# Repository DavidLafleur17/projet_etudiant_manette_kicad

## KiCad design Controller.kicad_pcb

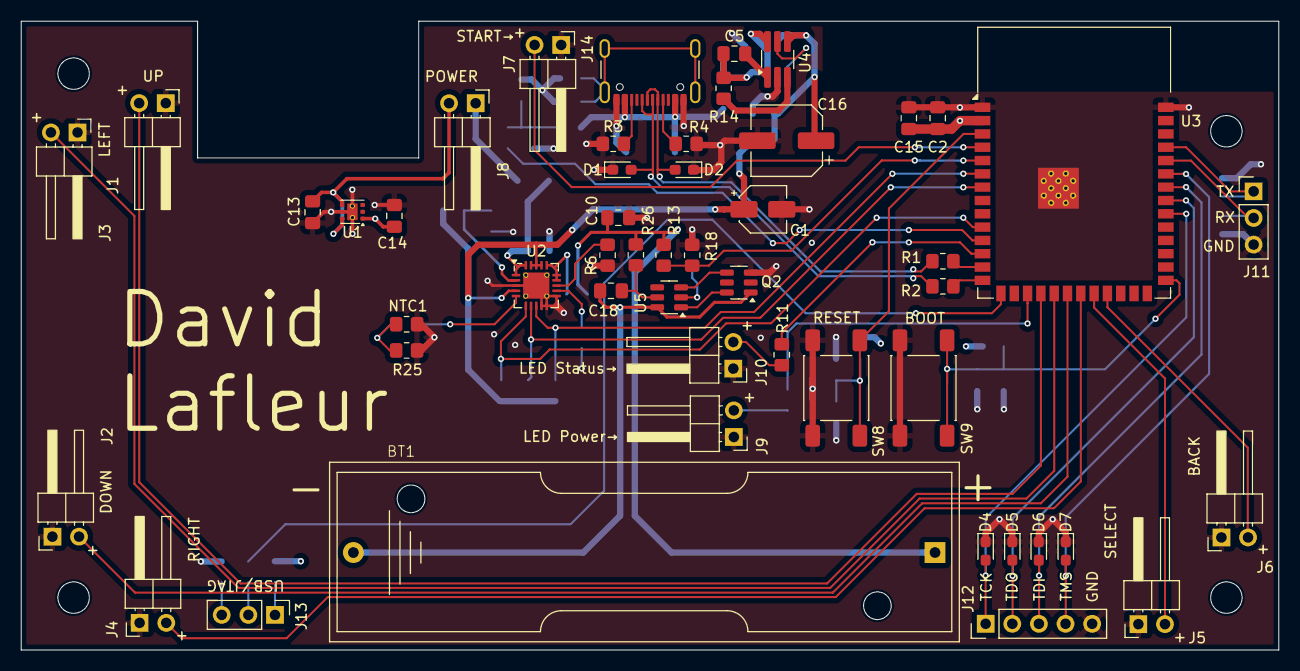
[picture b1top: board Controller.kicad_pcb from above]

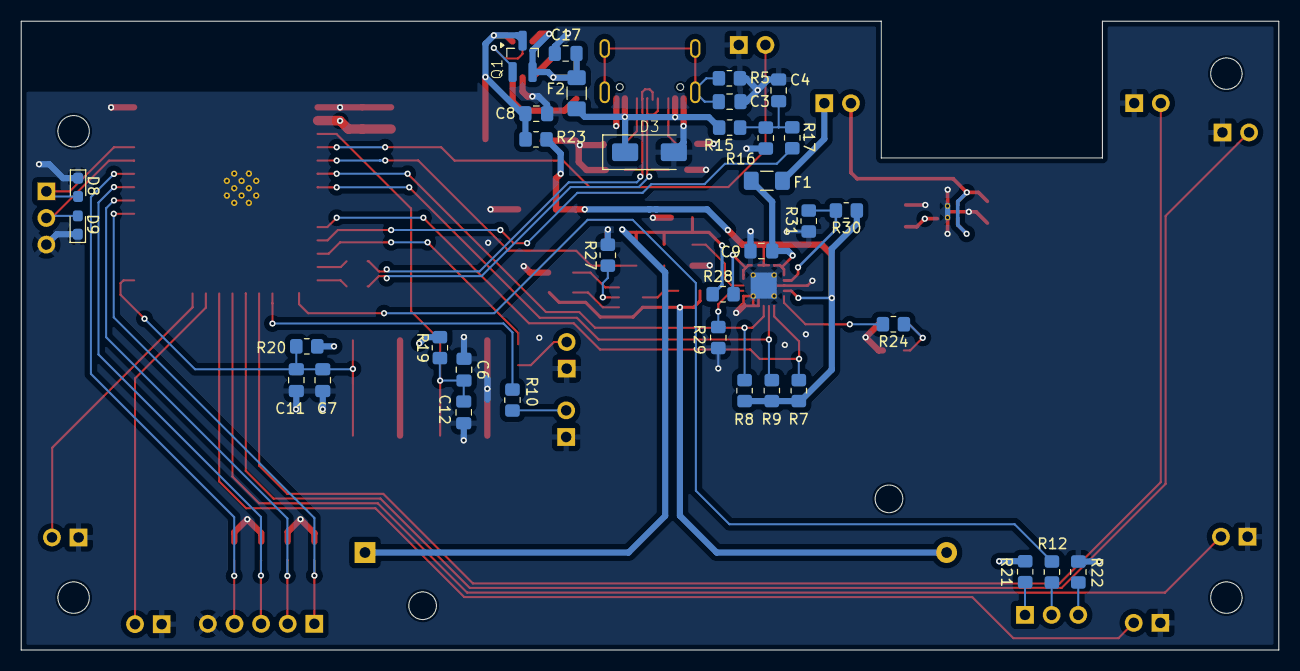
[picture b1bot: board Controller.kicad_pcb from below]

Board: 4 copper layers, 120.0 x 60.0 mm, 89 parts (35 on the bottom side), 60 nets.

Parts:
BT1: 3.7V 800mAh; BCAAPC
C1: 10uF; CP_Elec_4x5.4
C2, C3, C4, C5, C6, C7, C8, C18: 100nF; C_0805_2012Metric_Pad1.18x1.45mm_HandSolder
C9, C10: 4.7uF; C_0805_2012Metric_Pad1.18x1.45mm_HandSolder
C11, C12, C13, C14: 1uF; C_0805_2012Metric_Pad1.18x1.45mm_HandSolder
C15: 22uF; C_0805_2012Metric_Pad1.18x1.45mm_HandSolder
C16: 47uF; CP_Elec_6.3x5.9
C17: 22nF; C_0805_2012Metric_Pad1.18x1.45mm_HandSolder
D1, D2: ESD5V; D_0603_1608Metric_Pad1.05x0.95mm_HandSolder
D3: SMAJ5.0A; P6SMAJ5.0
D4, D5, D6, D7, D8, D9: ESD53V3; D_0603_1608Metric_Pad1.05x0.95mm_HandSolder
F1, F2: 750mA; Fuse_1206_3216Metric_Pad1.42x1.75mm_HandSolder
H1, H2, H3, H4: MountingHole; MountingHole_3mm
J1: Conn_UP; PinHeader_1x02_P2.54mm_Horizontal
J2: Conn_DOWN; PinHeader_1x02_P2.54mm_Horizontal
J3: Conn_LEFT; PinHeader_1x02_P2.54mm_Horizontal
J4: Conn_RIGHT; PinHeader_1x02_P2.54mm_Horizontal
J5: Conn_SELECT; PinHeader_1x02_P2.54mm_Horizontal
J6: Conn_BACK; PinHeader_1x02_P2.54mm_Horizontal
J7: Conn_START; PinHeader_1x02_P2.54mm_Horizontal
J8: Conn_POWER; PinHeader_1x02_P2.54mm_Horizontal
J9: Conn_LED_POWER; PinHeader_1x02_P2.54mm_Horizontal
J10: Conn_LED_STATUS; PinHeader_1x02_P2.54mm_Horizontal
J11: UART; PinHeader_1x03_P2.54mm_Vertical
J12: JTAG; PinHeader_1x05_P2.54mm_Vertical
J13: USB/JTAG; PinHeader_1x03_P2.54mm_Vertical
J14: USB_C_Receptacle_USB2.0_16P; USB_C_Receptacle_GCT_USB4105-xx-A_16P_TopMnt_Horizontal
NTC1: 10kΩ_{THERM}; R_0805_2012Metric_Pad1.20x1.40mm_HandSolder
Q1: NMOS; GSF3407
Q2: 8205A; SOT-23-6
R1, R2: 22Ω; R_0805_2012Metric_Pad1.20x1.40mm_HandSolder
R3, R4: 5.1kΩ; R_0805_2012Metric_Pad1.20x1.40mm_HandSolder
R5: 1MΩ; R_0805_2012Metric_Pad1.20x1.40mm_HandSolder
R6: 2.49kΩ; R_0805_2012Metric_Pad1.20x1.40mm_HandSolder
R7, R8, R9, R19, R20, R21, R22: 10kΩ; R_0805_2012Metric_Pad1.20x1.40mm_HandSolder
R10, R11, R12: 470Ω; R_0805_2012Metric_Pad1.20x1.40mm_HandSolder
R13, R15: 33kΩ; R_0805_2012Metric_Pad1.20x1.40mm_HandSolder
R14: 100kΩ; R_0805_2012Metric_Pad1.20x1.40mm_HandSolder
R16, R18: 47kΩ; R_0805_2012Metric_Pad1.20x1.40mm_HandSolder
R17, R27: 1kΩ; R_0805_2012Metric_Pad1.20x1.40mm_HandSolder
R23, R28: 0Ω; R_0805_2012Metric_Pad1.20x1.40mm_HandSolder
R24: 1.6kΩ; R_0805_2012Metric_Pad1.20x1.40mm_HandSolder
R25: 66.5kΩ; R_0805_2012Metric_Pad1.20x1.40mm_HandSolder
R26: 100Ω; R_0805_2012Metric_Pad1.20x1.40mm_HandSolder
R29: 24.9kΩ; R_0805_2012Metric_Pad1.20x1.40mm_HandSolder
R30: 330kΩ; R_0805_2012Metric_Pad1.20x1.40mm_HandSolder
R31: 110kΩ; R_0805_2012Metric_Pad1.20x1.40mm_HandSolder
SW8: B_MCU RST; SW_Push_1P1T_NO_E-Switch_TL3301NxxxxxG
SW9: B_BOOT; SW_Push_1P1T_NO_E-Switch_TL3301NxxxxxG
U1: LP5912-3.3DRV; WSON-6-1EP_2x2mm_P0.65mm_EP1x1.6mm_ThermalVias
U2: MCP73871; QFN-20-1EP_4x4mm_P0.5mm_EP2.5x2.5mm_ThermalVias
U3: ESP32-S3-WROOM-1 N8R8; ESP32-S3-WROOM-1
U4: AP74700Q; TSOT-23-6_HandSoldering
U5: DW01A; SOT-23-6

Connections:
+3.3V: C2.1, C14.1, C15.1, R19.2, R20.2, R21.1, U1.1 (OUT), U3.2 (3V3)
/3.3V_LDO/VIN: C13.1, J8.2, U1.4 (EN), U1.6 (IN)
/Boutons/BACK: J6.2, U3.23 (IO21)
/Boutons/DOWN: J2.2, U3.20 (IO12)
/Boutons/LED_Power: R10.2, U3.17 (IO9)
/Boutons/LED_Status: R11.2, U3.12 (IO8)
/Boutons/LEFT: J3.2, U3.19 (IO11)
/Boutons/RIGHT: J4.2, U3.21 (IO13)
/Boutons/SELECT: J5.2, U3.22 (IO14)
/Boutons/START: J7.2, U3.4 (IO4)
/Boutons/UP: J1.2, U3.18 (IO10)
/Circuit de charge/STAT1: R8.2, U2.8 (STAT1/~LBO), U3.6 (IO6)
/Circuit de charge/STAT2: R9.2, U2.7 (STAT2), U3.7 (IO7)
/Circuit de charge/VBAT_SENSE: R13.2, R18.1, U3.5 (IO5)
/Circuit de charge/VIN: C8.1, C16.1, Q1.1 (D), R23.1, U4.4 (CATHODE)
/Circuit de charge/~PG: R7.2, U2.6 (~PG), U3.10 (IO17)
/Microcontroller/RX: D9.2 (A2), J11.2, U3.36 (RXD0)
/Microcontroller/TCK: D4.2 (A2), J12.1, U3.32 (IO39)
/Microcontroller/TDI: D6.2 (A2), J12.3, U3.34 (IO41)
/Microcontroller/TDO: D5.2 (A2), J12.2, U3.33 (IO40)
/Microcontroller/TMS: D7.2 (A2), J12.4, U3.35 (IO42)
/Microcontroller/TX: D8.2 (A2), J11.1, U3.37 (TXD0)
/Microcontroller/USB_D+: D1.2 (A2), J14.A6 (D+), J14.B6 (D+), R2.2
/Microcontroller/USB_D-: D2.2 (A2), J14.A7 (D-), J14.B7 (D-), R1.2
/Microcontroller/VBUS_SENSE: R17.1, U3.11 (IO18)
GND: C1.2, C2.2, C3.2, C4.2, C6.2, C7.2, C8.2, C9.2, C10.2, C11.2, C12.2, C13.2, C14.2, C15.2, C16.2, C17.2, D1.1 (A1), D2.1 (A1), D3.2 (A2), D4.1 (A1), D5.1 (A1), D6.1 (A1), D7.1 (A1), D8.1 (A1), D9.1 (A1), J1.1, J2.1, J3.1, J4.1, J5.1, J6.1, J7.1, J9.1, J10.1, J11.3, J12.5, J14.A1 (GND), J14.A12 (GND), J14.B1 (GND), J14.B12 (GND), NTC1.1, Q2.3 (S2), R3.1, R4.1, R5.1, R6.1, R16.2, R18.2, R22.2, R25.2, R27.2, R29.2, R31.1, SW8.1, SW9.1, U1.5 (GND), U1.7 (EP), U2.3 (SEL), U2.9 (~TE), U2.10 (V_{SS}), U2.11 (V_{SS}), U2.21 (V_{SS}), U3.1 (GND), U3.40 (GND), U3.41 (GND), U4.2 (GND)
unnamed: BT1.1 (+), C10.1, R13.1, R26.1, R28.2
unnamed: BT1.2 (-), C18.2, Q2.1 (D1), U5.6 (GND)
unnamed: C4.1, R15.2, R16.1, R17.2
unnamed: C9.1, F1.1, U2.1 (OUT), U2.20 (OUT)
unnamed: D3.1 (A1), F2.1, J14.A4 (VBUS), J14.A9 (VBUS), J14.B4 (VBUS), J14.B9 (VBUS), R15.1
unnamed: F1.2, J8.1
unnamed: J9.2, R10.1
unnamed: J10.2, R11.1
unnamed: J13.1, R21.2
unnamed: J13.2, R12.1
unnamed: J13.3, R22.1
unnamed: J14.A5 (CC1), R4.2
unnamed: J14.B5 (CC2), R3.2
unnamed: C3.1, J14.S1 (SHIELD), R5.2
unnamed: NTC1.2, R24.1, R25.1
unnamed: Q1.2 (G), U4.5 (GATE)
unnamed: C5.1, C17.1, F2.2, Q1.3 (S), R14.2, U4.6 (ANODE)
unnamed: Q2.6 (G1), U5.1 (DO)
unnamed: Q2.4 (G2), U5.3 (CO)
unnamed: C1.1, R7.1, R8.1, R9.1, R23.2, R30.1, U2.4 (PROG2), U2.17 (CE), U2.18 (IN), U2.19 (IN)
unnamed: R6.2, U2.13 (PROG1)
unnamed: R29.1, U2.12 (PROG3)
unnamed: R24.2, U2.5 (THERM)
unnamed: R30.2, R31.2, U2.2 (VPCC)
unnamed: R28.1, U2.14 (V_{BAT}), U2.15 (V_{BAT}), U2.16 (V_{BAT_SENSE})
unnamed: C6.1, C12.1, R19.1, SW8.2, U3.3 (EN)
unnamed: C7.1, C11.1, R20.1, SW9.2, U3.27 (IO0)
unnamed: R12.2, U3.15 (IO3)
unnamed: R2.1, U3.14 (USB_D+)
unnamed: R1.1, U3.13 (USB_D-)
unnamed: R14.1, U4.3 (EN)
unnamed: C5.2, U4.1 (VCP)
unnamed: C18.1, R26.2, U5.5 (VCC)
unnamed: R27.1, U5.2 (VM)

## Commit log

2026-06-01 Schemas kicad pour manette lors du 31 mai 2026
